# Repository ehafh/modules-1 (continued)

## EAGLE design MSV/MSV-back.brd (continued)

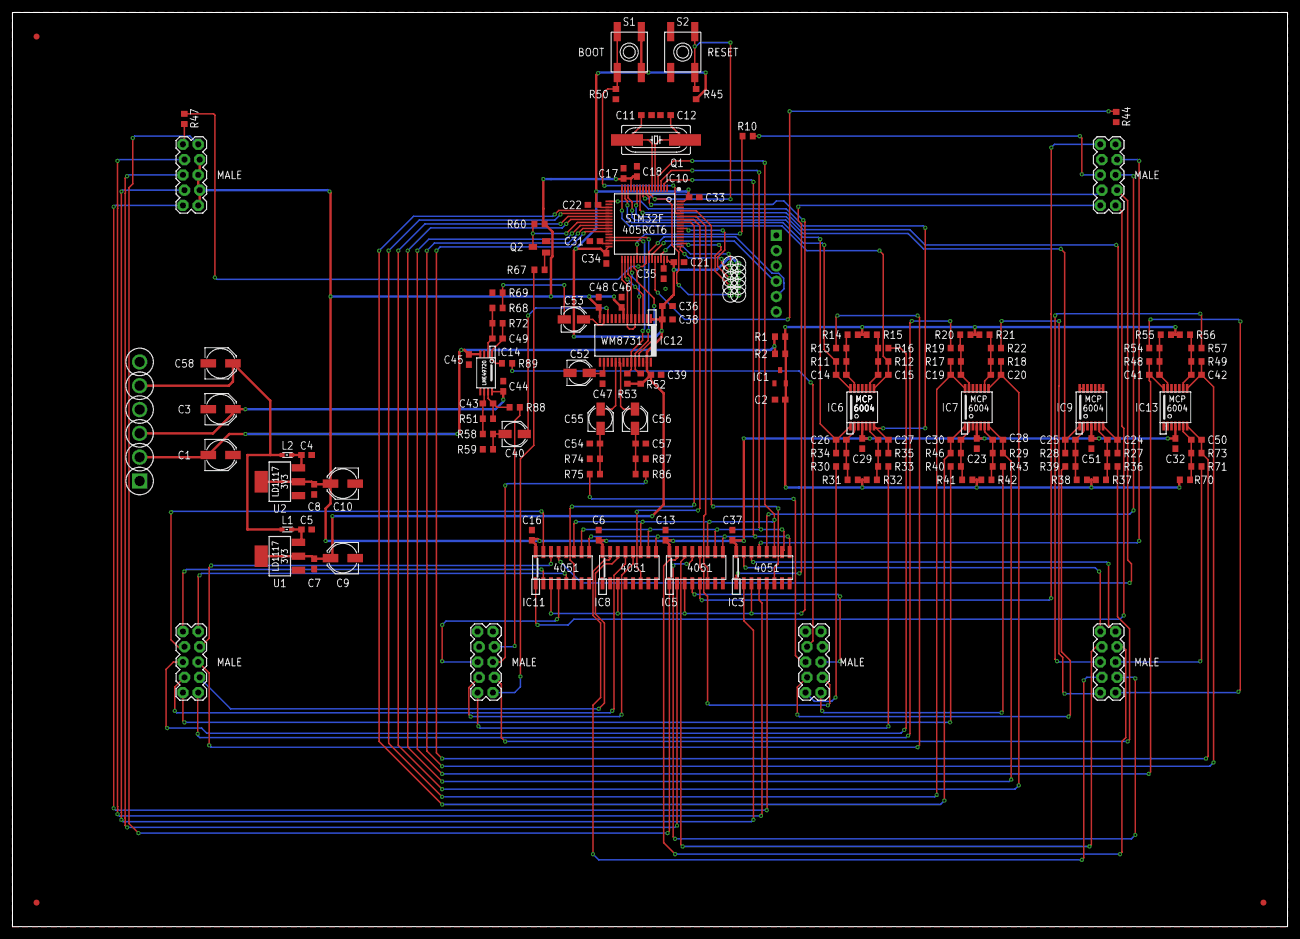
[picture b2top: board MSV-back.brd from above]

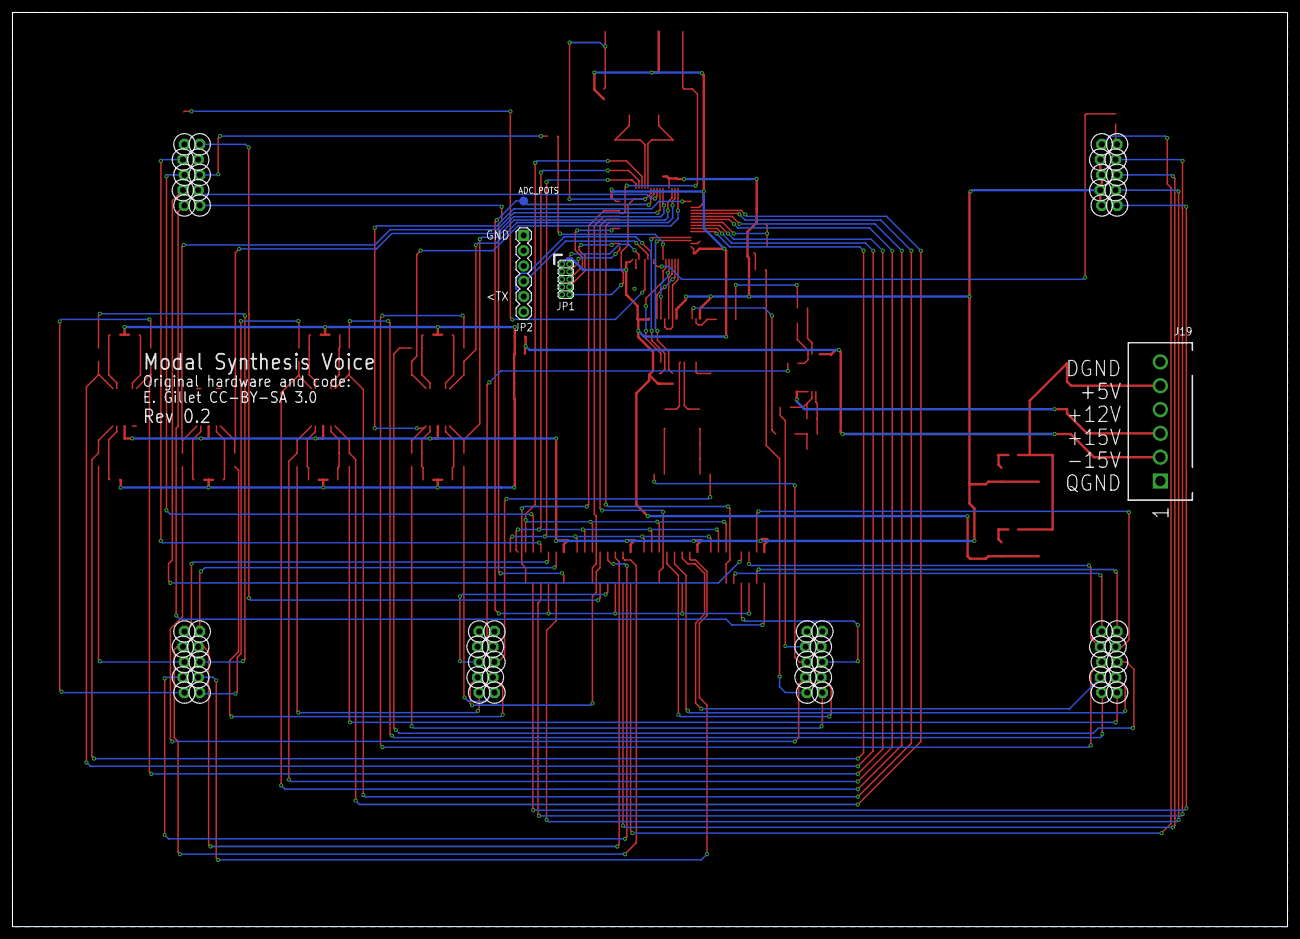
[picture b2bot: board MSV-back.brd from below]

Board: 2 copper layers, 212.0 x 152.0 mm, 153 parts (4 on the bottom side), 132 nets.

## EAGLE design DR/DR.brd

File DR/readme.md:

Overview
=======

Digital Resonator is a synthesizer module for the Buchla format, developed and manufactured by [1979](https://1979.ws/). It is based on [Rings](https://mutable-instruments.net/modules/rings/) by [Mutable Instruments](https://mutable-instruments.net/). The original source files for Rings can be found in the [Mutable Instruments](https://github.com/pichenettes/eurorack) Github repository.

Visit [1979.ws/digital-resonator](https://1979.ws/digital-resonator/) for more information.

License
=======

These schematic and PCB files are distributed under the Creative Commons [CC-BY-SA 3.0](https://creativecommons.org/licenses/by-sa/3.0/) license, the same license used by the original hardware.

CC BY-SA 3.0 does not confer the right to use intellectual property such as trademarks, brand names, and logos. 1979, Digital Resonator, Mutable Instruments, and Rings are trademarks of their respective owners and should not be used without permission.

Firmware
=======

Source code will be published soon.

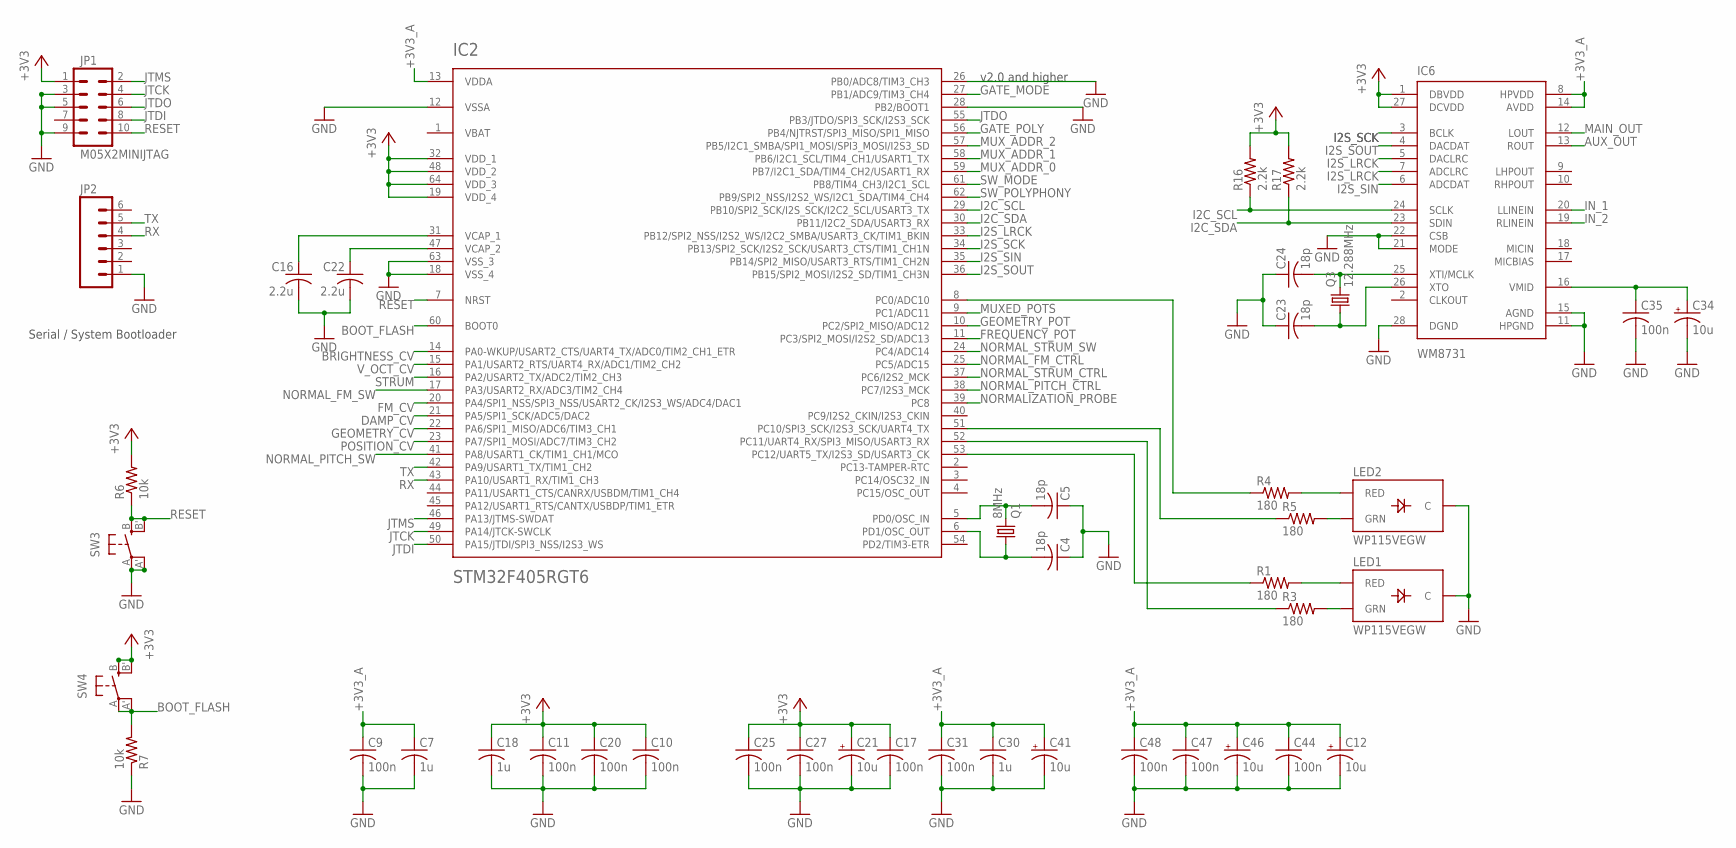
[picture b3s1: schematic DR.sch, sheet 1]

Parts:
C4, C5, C23, C24: 18p; C0603
C7, C18, C30: 1u; C0603
C9, C10, C11, C17, C20, C25, C27, C31, C35, C44, C47, C48: 100n; C0603
C12, C21, C34, C41, C46: 10u; PANASONIC_A
C16, C22: 2.2u; C0805
IC2: STM32F405RGT6; TQFP-10X10-64
IC6: WM8731; SSOP28
JP1: M05X2MINIJTAG; 2X5-1.27
JP2: M06SIP; 1X06
LED1, LED2: WP115VEGW; LED-BICOLOR-THROUGHHOLE
Q1: 8MHz; HC49UP
Q3: 12.288MHz; HC49UP
R1, R3, R4, R5: 180; R0603
R6, R7: 10k; R0603
R16, R17: 2.2k; R0603
SW3, SW4: EVQQ2; EVQ-Q2

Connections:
+3V3: C10.1, C11.1, C17.1, C18.1, C20.1, C21.+, C25.1, C27.1, IC2.19 (VDD_4), IC2.32 (VDD_1), IC2.48 (VDD_2), IC2.64 (VDD_3), IC6.1 (DBVDD), IC6.27 (DCVDD), JP1.1, R6.2, R16.2, R17.2, SW4.B (S), SW4.B' (S1); also elsewhere on the board
+3V3_A: C7.1, C9.1, C12.+, C30.1, C31.1, C41.+, C44.1, C46.+, C47.1, C48.1, IC2.13 (VDDA), IC6.8 (HPVDD), IC6.14 (AVDD); also elsewhere on the board
AUX_OUT: IC6.13 (ROUT); also elsewhere on the board
BOOT_FLASH: IC2.60 (BOOT0), R7.2, SW4.A, SW4.A' (P1)
BRIGHTNESS_CV: IC2.14 (PA0-WKUP/USART2_CTS/UART4_TX/ADC0/TIM2_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); also elsewhere on the board
DAMP_CV: IC2.21 (PA5/SPI1_SCK/ADC5/DAC2); also elsewhere on the board
FM_CV: IC2.20 (PA4/SPI1_NSS/SPI3_NSS/USART2_CK/I2S3_WS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); also elsewhere on the board
FREQUENCY_POT: IC2.11 (PC3/SPI2_MOSI/I2S2_SD/ADC13); also elsewhere on the board
GATE_MODE: IC2.27 (PB1/ADC9/TIM3_CH4); also elsewhere on the board
GATE_POLY: IC2.56 (PB4/NJTRST/SPI3_MISO/SPI1_MISO); also elsewhere on the board
GEOMETRY_CV: IC2.22 (PA6/SPI1_MISO/ADC6/TIM3_CH1); also elsewhere on the board
GEOMETRY_POT: IC2.10 (PC2/SPI2_MISO/ADC12); also elsewhere on the board
GND: C4.1, C5.1, C7.2, C9.2, C10.2, C11.2, C12.-, C16.2, C17.2, C18.2, C20.2, C21.-, C22.2, C23.1, C24.1, C25.2, C27.2, C30.2, C31.2, C34.-, C35.2, C41.-, C44.2, C46.-, C47.2, C48.2, IC2.12 (VSSA), IC2.18 (VSS_4), IC2.26 (PB0/ADC8/TIM3_CH3), IC2.28 (PB2/BOOT1), IC2.63 (VSS_3), IC6.11 (HPGND), IC6.15 (AGND), IC6.21 (MODE), IC6.22 (CSB), IC6.28 (DGND), JP1.3, JP1.5, JP1.9, JP2.1, LED1.2 (C), LED2.2 (C), R7.1, SW3.A, SW3.A' (P1); also elsewhere on the board
I2C_SCL: IC2.29 (PB10/SPI2_SCK/I2S_SCK/I2C2_SCL/USART3_TX), IC6.24 (SCLK), R16.1
I2C_SDA: IC2.30 (PB11/I2C2_SDA/USART3_RX), IC6.23 (SDIN), R17.1
I2S_LRCK: IC2.33 (PB12/SPI2_NSS/I2S2_WS/I2C2_SMBA/USART3_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), IC6.5 (DACLRC), IC6.7 (ADCLRC)
I2S_SCK: IC2.34 (PB13/SPI2_SCK/I2S2_SCK/USART3_CTS/TIM1_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), IC6.3 (BCLK)
I2S_SIN: IC2.35 (PB14/SPI2_MISO/USART3_RTS/TIM1_CH2N), IC6.6 (ADCDAT)
I2S_SOUT: IC2.36 (PB15/SPI2_MOSI/I2S2_SD/TIM1_CH3N), IC6.4 (DACDAT)
IN_1: IC6.20 (LLINEIN); also elsewhere on the board
IN_2: IC6.19 (RLINEIN); also elsewhere on the board
JTCK: IC2.49 (PA14/JTCK-SWCLK), JP1.4
JTDI: IC2.50 (PA15/JTDI/SPI3_NSS/I2S3_WS), JP1.8
JTDO: IC2.55 (PB3/JTDO/SPI3_SCK/I2S3_SCK), JP1.6
JTMS: IC2.46 (PA13/JTMS-SWDAT), JP1.2
MAIN_OUT: IC6.12 (LOUT); also elsewhere on the board
MUXED_POTS: IC2.9 (PC1/ADC11); also elsewhere on the board
MUX_ADDR_0: IC2.59 (PB7/I2C1_SDA/TIM4_CH2/USART1_RX); also elsewhere on the board
MUX_ADDR_1: IC2.58 (PB6/I2C1_SCL/TIM4_CH1/USART1_TX); also elsewhere on the board
MUX_ADDR_2: IC2.57 (PB5/I2C1_SMBA/SPI1_MOSI/SPI3_MOSI/I2S3_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); also elsewhere on the board
unnamed: C5.2, IC2.5 (PD0/OSC_IN), Q1.2
unnamed: C4.2, IC2.6 (PD1/OSC_OUT), Q1.1
unnamed: LED1.3 (RED), R1.2
unnamed: C22.1, IC2.47 (VCAP_2)
unnamed: C34.+, C35.1, IC6.16 (VMID)
unnamed: C16.1, IC2.31 (VCAP_1)
unnamed: LED1.1 (GRN), R3.2
unnamed: LED2.3 (RED), R4.2
unnamed: LED2.1 (GRN), R5.2
unnamed: IC2.52 (PC11/UART4_RX/SPI3_MISO/USART3_RX), R3.1
unnamed: IC2.8 (PC0/ADC10), R4.1
unnamed: C24.2, IC6.25 (XTI/MCLK), Q3.2
unnamed: C23.2, IC6.26 (XTO), Q3.1
unnamed: IC2.53 (PC12/UART5_TX/I2S3_SD/USART3_CK), R1.1
unnamed: IC2.51 (PC10/SPI3_SCK/I2S3_SCK/UART4_TX), R5.1
NORMALIZATION_PROBE: IC2.39 (PC8); also elsewhere on the board
NORMAL_FM_CTRL: IC2.25 (PC5/ADC15); also elsewhere on the board
NORMAL_FM_SW: IC2.17 (PA3/USART2_RX/ADC3/TIM2_CH4); also elsewhere on the board
NORMAL_PITCH_CTRL: IC2.38 (PC7/I2S3_MCK); also elsewhere on the board
NORMAL_PITCH_SW: IC2.41 (PA8/USART1_CK/TIM1_CH1/MCO); also elsewhere on the board
NORMAL_STRUM_CTRL: IC2.37 (PC6/I2S2_MCK); also elsewhere on the board
NORMAL_STRUM_SW: IC2.24 (PC4/ADC14); also elsewhere on the board
POSITION_CV: IC2.23 (PA7/SPI1_MOSI/ADC7/TIM3_CH2); also elsewhere on the board
RESET: IC2.7 (NRST), JP1.10, R6.1, SW3.B (S), SW3.B' (S1)
RX: IC2.43 (PA10/USART1_RX/TIM1_CH3), JP2.4
STRUM: IC2.16 (PA2/USART2_TX/ADC2/TIM2_CH3); also elsewhere on the board
SW_MODE: IC2.61 (PB8/TIM4_CH3/I2C1_SCL); also elsewhere on the board
SW_POLYPHONY: IC2.62 (PB9/SPI2_NSS/I2S2_WS/I2C1_SDA/TIM4_CH4); also elsewhere on the board
TX: IC2.42 (PA9/USART1_TX/TIM1_CH2), JP2.5
VBAT: IC2.1 (VBAT)
V_OCT_CV: IC2.15 (PA1/USART2_RTS/UART4_RX/ADC1/TIM2_CH2); also elsewhere on the board

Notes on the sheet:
Serial / System Bootloader
v2.0 and higher

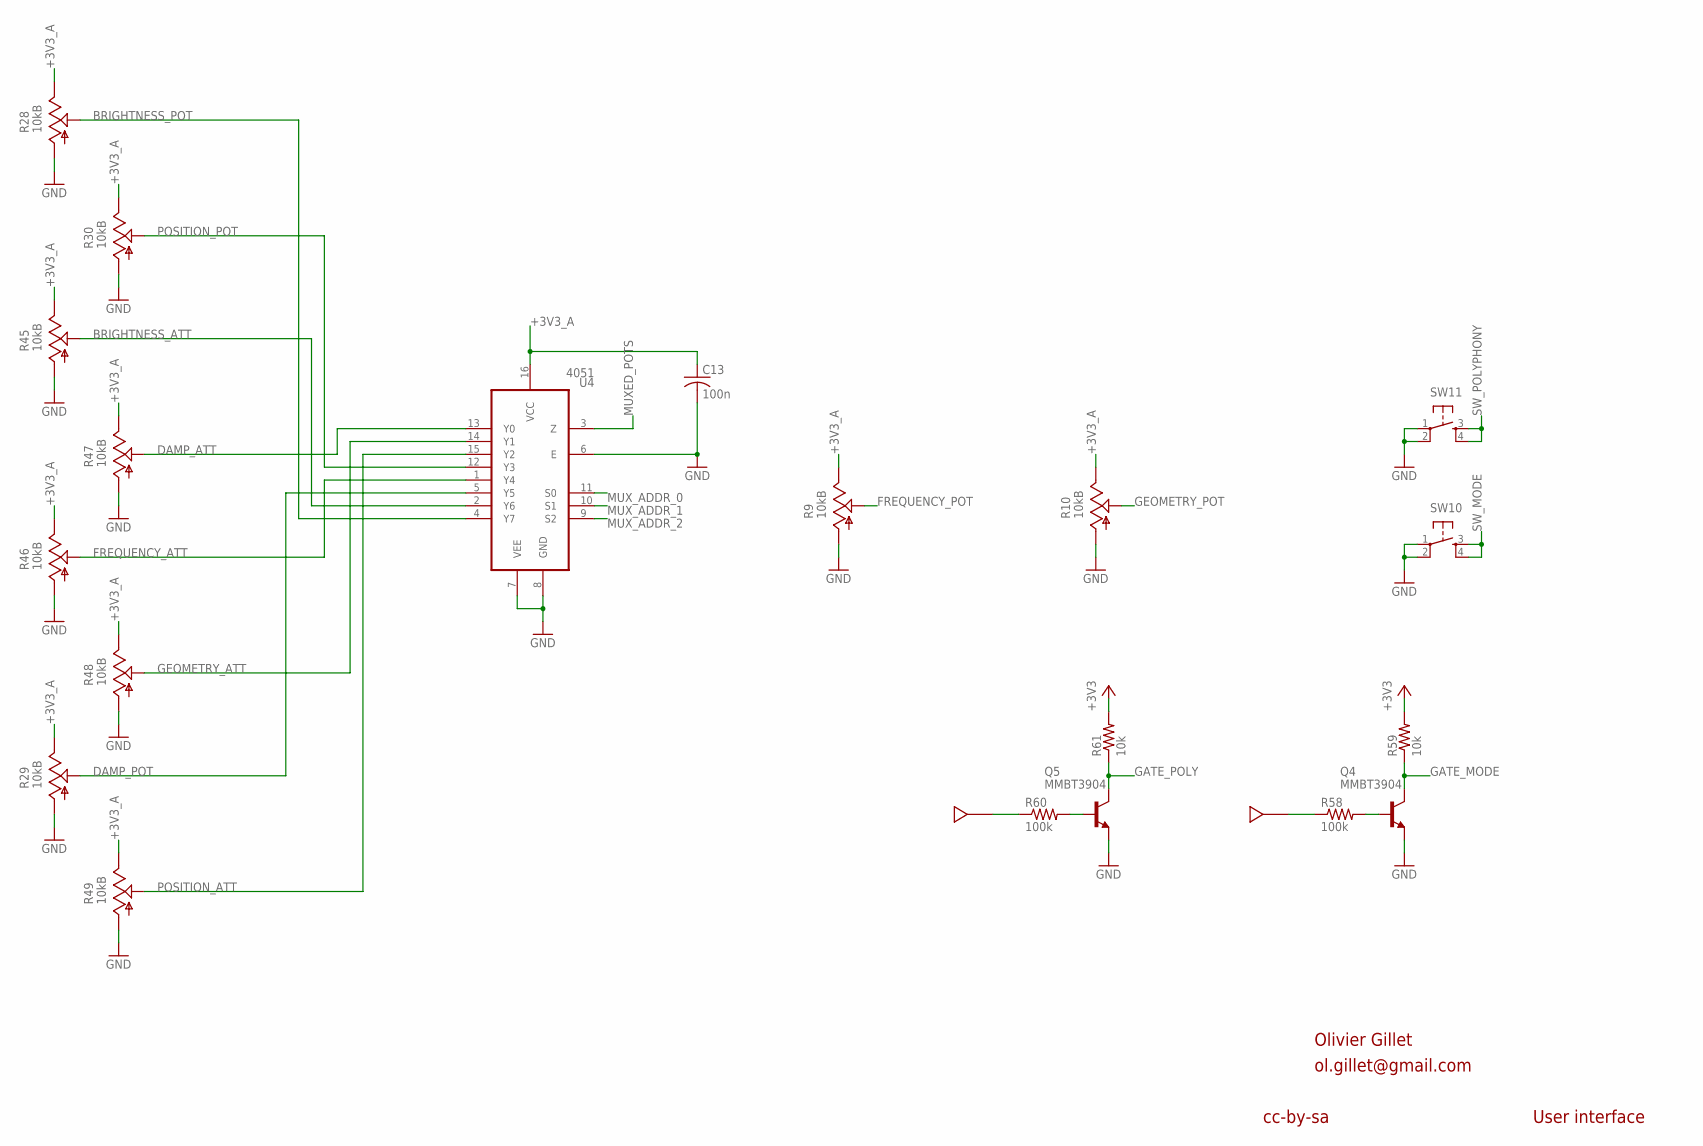
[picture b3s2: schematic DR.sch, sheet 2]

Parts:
C13: 100n; C0603
J7, J13: JOHNSON_BANANASTD; JOHNSON
Q4, Q5: MMBT3904; SOT23-BEC
R9, R10, R28, R29, R30: 10kB; ALPS_POT_VERTICAL_PS
R45, R46, R47, R48, R49: 10kB; ALPS_POT_VERTICAL
R58, R60: 100k; R0603
R59, R61: 10k; R0603
SW10, SW11: TAC_SWITCH; C&K_D6R
U4: 4051; SO16

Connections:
+3V3: R59.2, R61.2; also elsewhere on the board
+3V3_A: C13.1, R9.P$1 (E), R10.P$1 (E), R28.P$1 (E), R29.P$1 (E), R30.P$1 (E), R45.P$1 (E), R46.P$1 (E), R47.P$1 (E), R48.P$1 (E), R49.P$1 (E), U4.16 (VCC); also elsewhere on the board
BRIGHTNESS_ATT: R45.P$2 (S), U4.2 (Y6)
BRIGHTNESS_POT: R28.P$2 (S), U4.4 (Y7)
DAMP_ATT: R47.P$2 (S), U4.13 (Y0)
DAMP_POT: R29.P$2 (S), U4.5 (Y5)
FREQUENCY_ATT: R46.P$2 (S), U4.1 (Y4)
FREQUENCY_POT: R9.P$2 (S); also elsewhere on the board
GATE_MODE: Q4.C, R59.1; also elsewhere on the board
GATE_POLY: Q5.C, R61.1; also elsewhere on the board
GEOMETRY_ATT: R48.P$2 (S), U4.14 (Y1)
GEOMETRY_POT: R10.P$2 (S); also elsewhere on the board
GND: C13.2, Q4.E, Q5.E, R9.P$3 (A), R10.P$3 (A), R28.P$3 (A), R29.P$3 (A), R30.P$3 (A), R45.P$3 (A), R46.P$3 (A), R47.P$3 (A), R48.P$3 (A), R49.P$3 (A), SW10.1, SW10.2, SW11.1, SW11.2, U4.6 (E), U4.7 (VEE), U4.8 (GND); also elsewhere on the board
MUXED_POTS: U4.3 (Z); also elsewhere on the board
MUX_ADDR_0: U4.11 (S0); also elsewhere on the board
MUX_ADDR_1: U4.10 (S1); also elsewhere on the board
MUX_ADDR_2: U4.9 (S2); also elsewhere on the board
unnamed: Q4.B, R58.2
unnamed: Q5.B, R60.2
unnamed: J7.1, R58.1
unnamed: J13.1, R60.1
POSITION_ATT: R49.P$2 (S), U4.15 (Y2)
POSITION_POT: R30.P$2 (S), U4.12 (Y3)
SW_MODE: SW10.3, SW10.4; also elsewhere on the board
SW_POLYPHONY: SW11.3, SW11.4; also elsewhere on the board

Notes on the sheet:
cc-by-sa
Olivier Gillet
ol.gillet@gmail.com
User interface

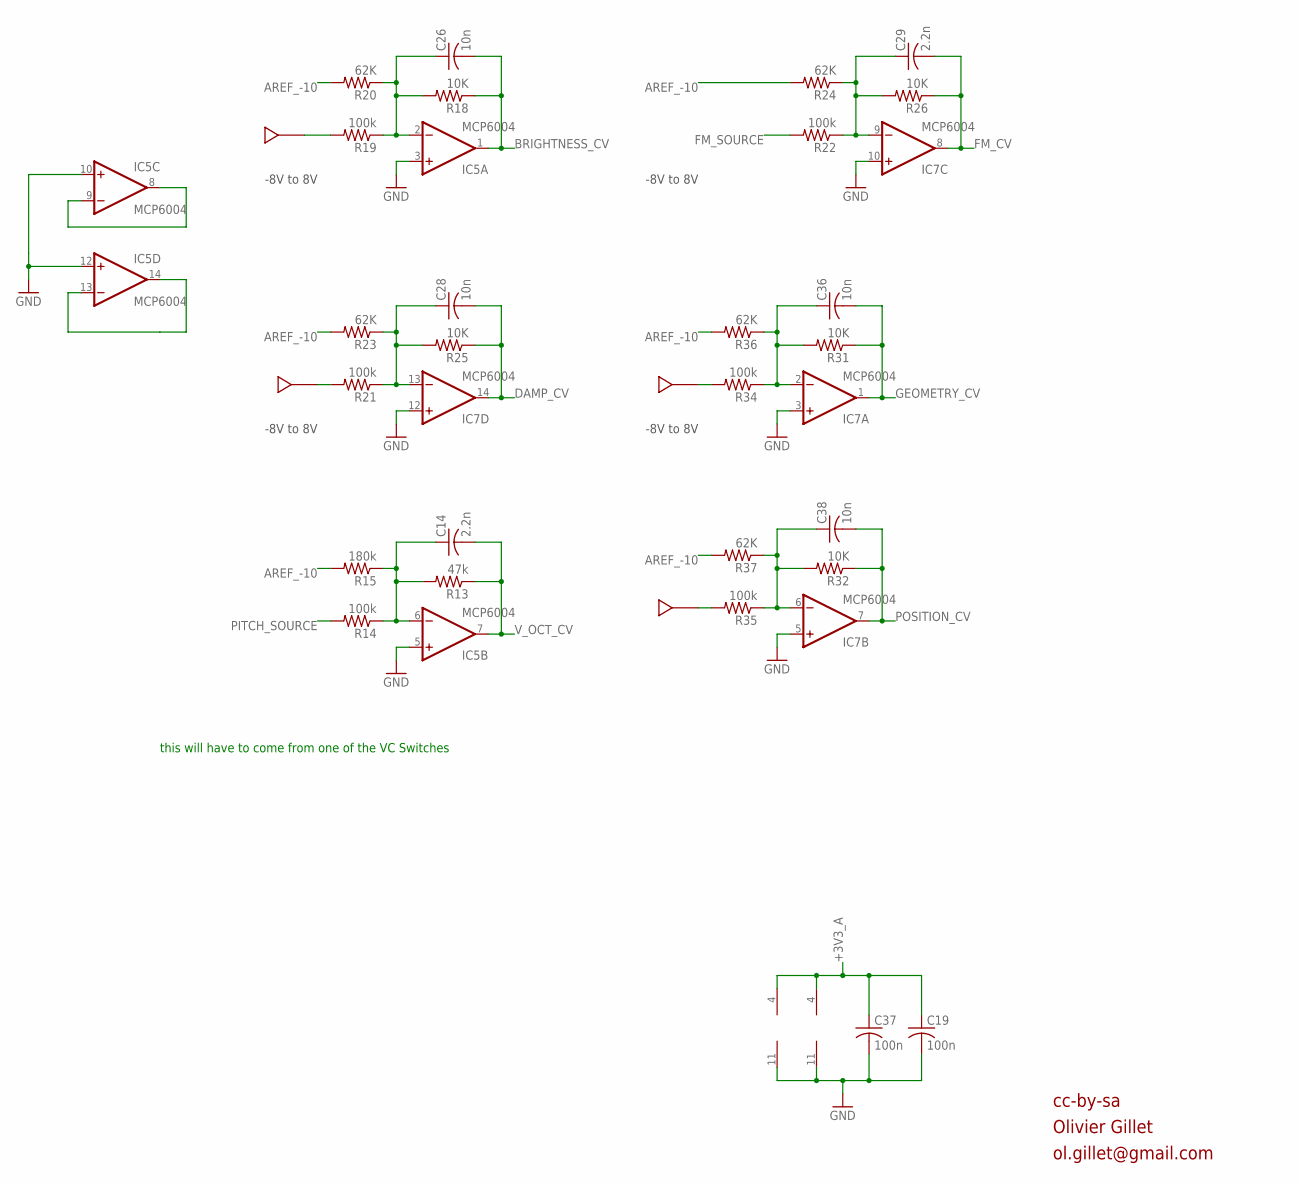
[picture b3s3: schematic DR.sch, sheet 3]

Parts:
C14, C29: 2.2n; C0603
C19, C37: 100n; C0603
C26, C28, C36, C38: 10n; C0603
IC5, IC7: MCP6004; SO14
J1, J3, J4, J14: JOHNSON_BANANASTD; JOHNSON
R13: 47k; R0603
R14, R19, R21, R22, R34, R35: 100k; R0603
R15: 180k; R0603
R18, R25, R26, R31, R32: 10K; R0603
R20, R23, R24, R36, R37: 62K; R0603

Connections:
+3V3_A: C19.1, C37.1, IC5.4 (V+), IC7.4 (V+); also elsewhere on the board
AREF_-10: R15.2, R20.2, R23.2, R24.2, R36.2, R37.2; also elsewhere on the board
BRIGHTNESS_CV: C26.2, IC5.1 (OUT), R18.1; also elsewhere on the board
DAMP_CV: C28.2, IC7.14 (OUT), R25.1; also elsewhere on the board
FM_CV: C29.2, IC7.8 (OUT), R26.1; also elsewhere on the board
FM_SOURCE: R22.2; also elsewhere on the board
GEOMETRY_CV: C36.2, IC7.1 (OUT), R31.1; also elsewhere on the board
GND: C19.2, C37.2, IC5.3 (+IN), IC5.5 (+IN), IC5.10 (+IN), IC5.11 (V-), IC5.12 (+IN), IC7.3 (+IN), IC7.5 (+IN), IC7.10 (+IN), IC7.11 (V-), IC7.12 (+IN); also elsewhere on the board
unnamed: J14.1, R19.2
unnamed: C26.1, IC5.2 (-IN), R18.2, R19.1, R20.1
unnamed: C29.1, IC7.9 (-IN), R22.1, R24.1, R26.2
unnamed: J4.1, R34.2
unnamed: J1.1, R21.2
unnamed: C28.1, IC7.13 (-IN), R21.1, R23.1, R25.2
unnamed: C14.1, IC5.6 (-IN), R13.2, R14.1, R15.1
unnamed: C36.1, IC7.2 (-IN), R31.2, R34.1, R36.1
unnamed: J3.1, R35.2
unnamed: C38.1, IC7.6 (-IN), R32.2, R35.1, R37.1
unnamed: IC5.13 (-IN), IC5.14 (OUT)
unnamed: IC5.8 (OUT), IC5.9 (-IN)
PITCH_SOURCE: R14.2; also elsewhere on the board
POSITION_CV: C38.2, IC7.7 (OUT), R32.1; also elsewhere on the board
V_OCT_CV: C14.2, IC5.7 (OUT), R13.1; also elsewhere on the board

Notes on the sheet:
cc-by-sa
Olivier Gillet
ol.gillet@gmail.com
-8V to 8V
this will have to come from one of the VC Switches

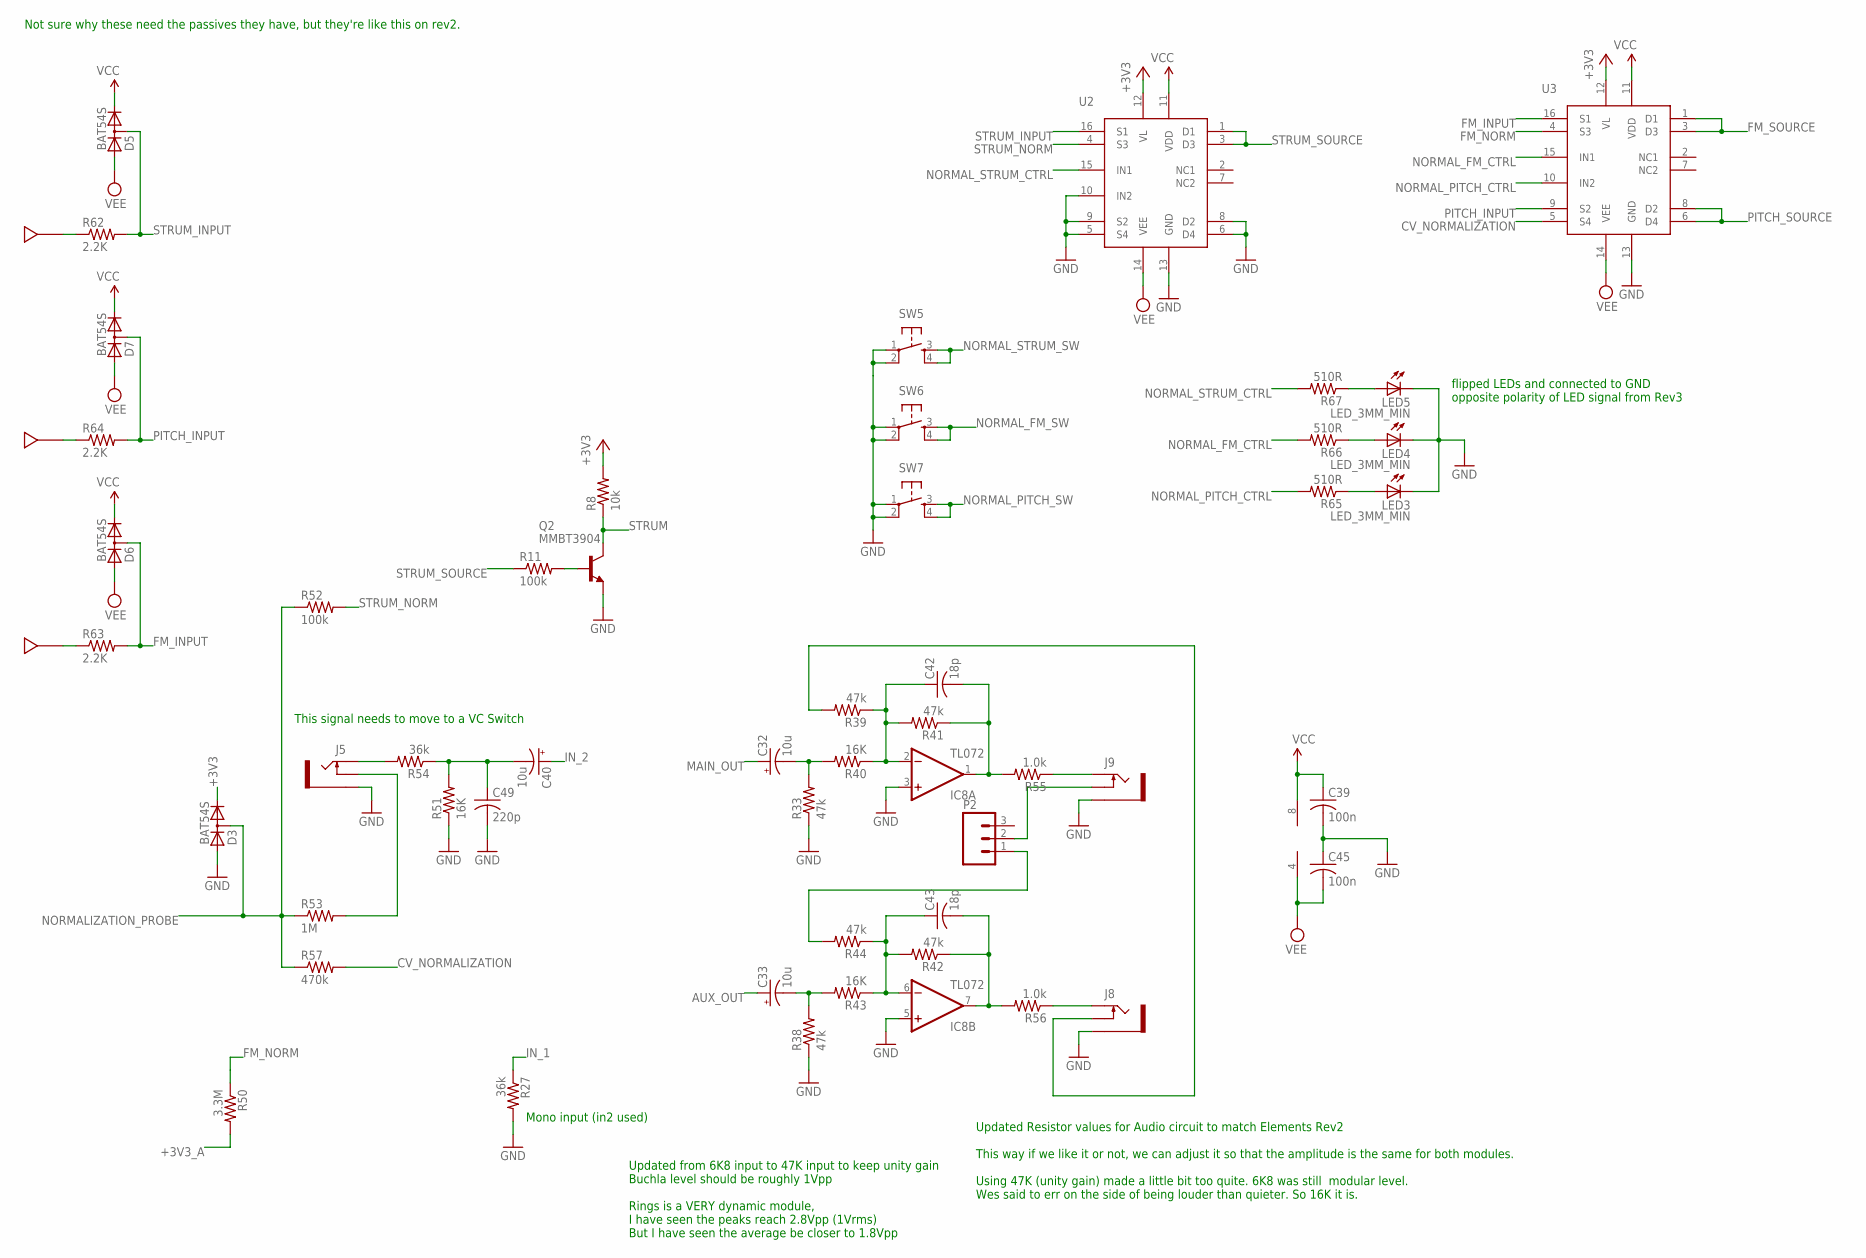
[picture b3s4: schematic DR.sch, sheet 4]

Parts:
C32, C33, C40: 10u; PANASONIC_A
C39, C45: 100n; C0603
C42, C43: 18p; C0603
C49: 220p; C0603
D3, D5, D6, D7: BAT54S; SOT23
IC8: TL072; SO08
J2, J6, J12: JOHNSON_BANANASTD; JOHNSON
J5, J8, J9: SWITCHCRAFT_42A; SWITCH_JOHNSON
LED3, LED4, LED5: LED_3MM_MIN
P2: M03LOCK; 1X03_LOCK
Q2: MMBT3904; SOT23-BEC
R8: 10k; R0603
R11, R52: 100k; R0603
R27, R54: 36k; R0603
R33, R38, R39, R41, R42, R44: 47k; R0603
R40, R43, R51: 16K; R0603
R50: 3.3M; R0603
R53: 1M; R0603
R55, R56: 1.0k; R0603
R57: 470k; R0603
R62, R63, R64: 2.2K; R0603
R65, R66, R67: 510R; R0603
SW5, SW6, SW7: TAC_SWITCHPTH; TACTILE-PTH
U2, U3: DG403_ANALOG_SWITCH; SO16

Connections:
+3V3: D3.2 (C), R8.2, U2.12 (VL), U3.12 (VL); also elsewhere on the board
+3V3_A: R50.2; also elsewhere on the board
AUX_OUT: C33.+; also elsewhere on the board
CV_NORMALIZATION: R57.2, U3.5 (S4)
FM_INPUT: D6.3 (AC), R63.2, U3.16 (S1)
FM_NORM: R50.1, U3.4 (S3)
FM_SOURCE: U3.1 (D1), U3.3 (D3); also elsewhere on the board
GND: C39.2, C45.1, C49.2, D3.1 (A), IC8.3 (+IN), IC8.5 (+IN), J5.G (1), J8.G (1), J9.G (1), LED3.K (C), LED4.K (C), LED5.K (C), Q2.E, R27.2, R33.1, R38.1, R51.1, SW5.1, SW5.2, SW6.1, SW6.2, SW7.1, SW7.2, U2.5 (S4), U2.6 (D4), U2.8 (D2), U2.9 (S2), U2.10 (IN2), U2.13 (GND), U3.13 (GND); also elsewhere on the board
IN_1: R27.1; also elsewhere on the board
IN_2: C40.+; also elsewhere on the board
MAIN_OUT: C32.+; also elsewhere on the board
unnamed: C40.-, C49.1, R51.2, R54.1
unnamed: J5.S (3), R54.2
unnamed: C33.-, R38.2, R43.2
unnamed: LED5.A, R67.1
unnamed: C43.1, IC8.6 (-IN), R42.2, R43.1, R44.1
unnamed: C43.2, IC8.7 (OUT), R42.1, R56.2
unnamed: J8.S (3), R56.1
unnamed: C32.-, R33.2, R40.2
unnamed: C42.1, IC8.2 (-IN), R39.1, R40.1, R41.2
unnamed: C42.2, IC8.1 (OUT), R41.1, R55.2
unnamed: J9.S (3), R55.1
unnamed: LED4.A, R66.1
unnamed: J12.1, R62.1
unnamed: J5.C (2), R53.2
unnamed: J8.C (2), R39.2
unnamed: P2.1, R44.2
unnamed: J9.C (2), P2.2
unnamed: LED3.A, R65.1
unnamed: J2.1, R63.1
unnamed: J6.1, R64.1
unnamed: Q2.B, R11.2
NORMALIZATION_PROBE: D3.3 (AC), R52.1, R53.1, R57.1; also elsewhere on the board
NORMAL_FM_CTRL: R66.2, U3.15 (IN1); also elsewhere on the board
NORMAL_FM_SW: SW6.3, SW6.4; also elsewhere on the board
NORMAL_PITCH_CTRL: R65.2, U3.10 (IN2); also elsewhere on the board
NORMAL_PITCH_SW: SW7.3, SW7.4; also elsewhere on the board
NORMAL_STRUM_CTRL: R67.2, U2.15 (IN1); also elsewhere on the board
NORMAL_STRUM_SW: SW5.3, SW5.4; also elsewhere on the board
PITCH_INPUT: D7.3 (AC), R64.2, U3.9 (S2)
PITCH_SOURCE: U3.6 (D4), U3.8 (D2); also elsewhere on the board
STRUM: Q2.C, R8.1; also elsewhere on the board
STRUM_INPUT: D5.3 (AC), R62.2, U2.16 (S1)
STRUM_NORM: R52.2, U2.4 (S3)
STRUM_SOURCE: R11.1, U2.1 (D1), U2.3 (D3)
VCC: C39.1, D5.2 (C), D6.2 (C), D7.2 (C), IC8.8 (V+), U2.11 (VDD), U3.11 (VDD); also elsewhere on the board
VEE: C45.2, D5.1 (A), D6.1 (A), D7.1 (A), IC8.4 (V-), U2.14 (VEE), U3.14 (VEE); also elsewhere on the board

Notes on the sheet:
This signal needs to move to a VC Switch
Not sure why these need the passives they have, but they're like this on rev2.
Mono input (in2 used)
flipped LEDs and connected to GND opposite polarity of LED signal from Rev3
Updated from 6K8 input to 47K input to keep unity gain Buchla level should be roughly 1Vpp Rings is a VERY dynamic module, I have seen the peaks reach 2.8Vpp (1Vrms) But I have seen the average be closer to 1.8Vpp
Updated Resistor values for Audio circuit to match Elements Rev2 This way if we like it or not, we can adjust it so that the amplitude is the same for both modules. Using 47K (unity gain) made a little bit too quite. 6K8 was still modular level. Wes said to err on the side of being louder than quie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

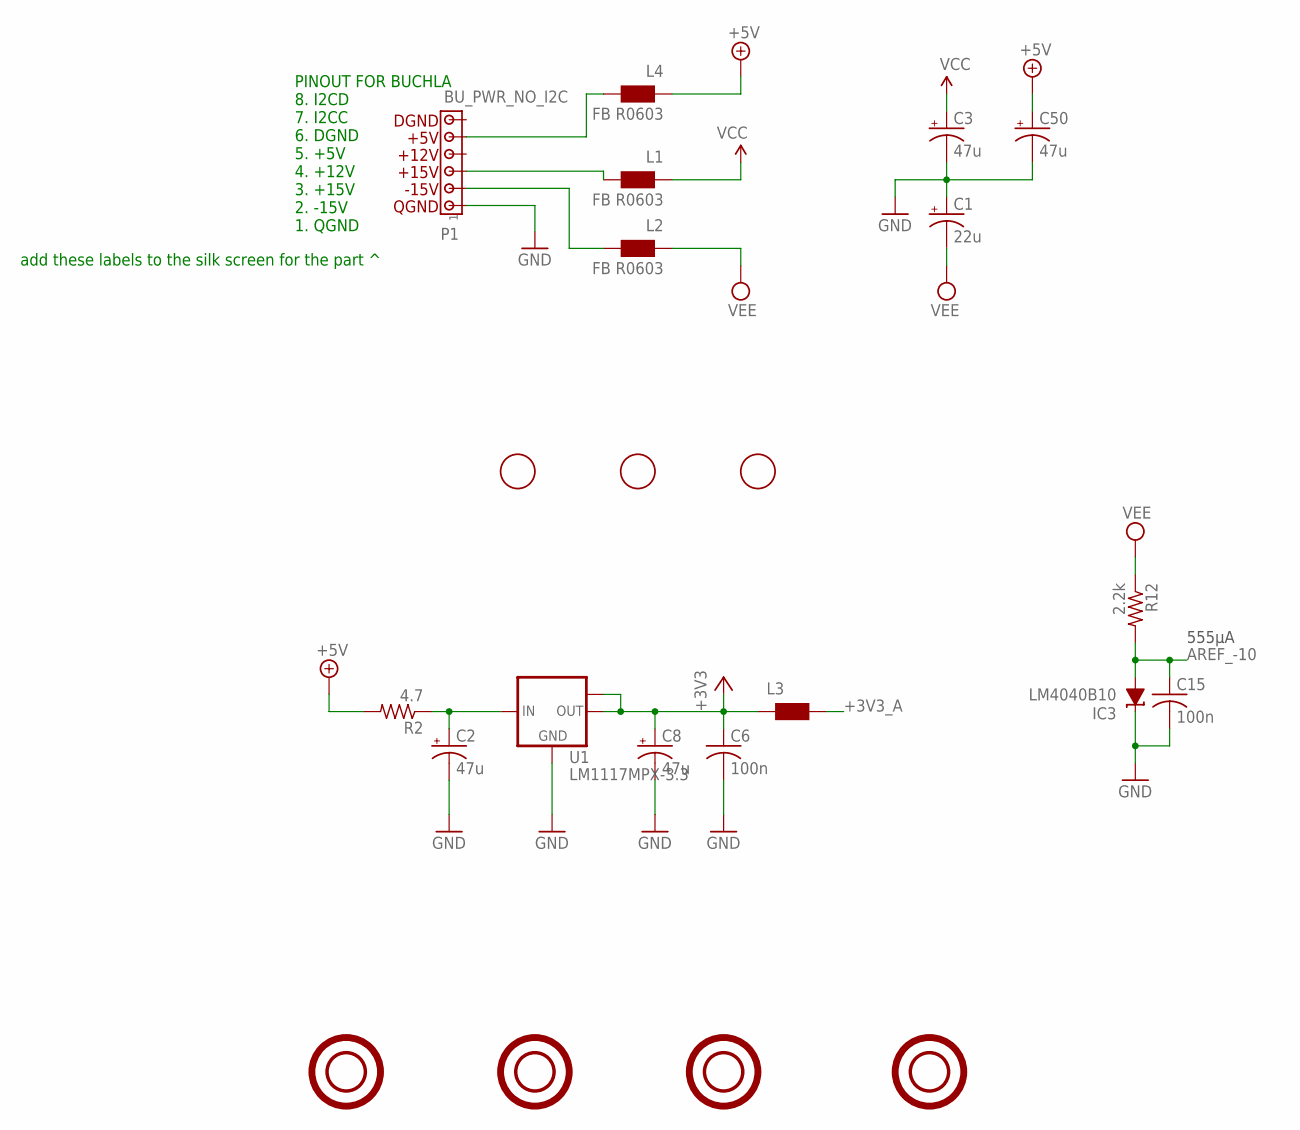
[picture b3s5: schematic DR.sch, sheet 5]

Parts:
C1: 22u; PANASONIC_C
C2, C3, C8, C50: 47u; PANASONIC_D
C6, C15: 100n; C0603
FD1, FD2, FD3: FIDUCIAL; FIDUCIAL_1MM
H1, H2, H3, H4: 3MM_MOUNT_HOLE; 3,0-PAD
IC3: LM4040B10; DBZ_R-PDSO-G3
L1, L2, L4: FB R0603; 0603
L3: WE-CBF_0603; 0603
P1: BU_PWR_NO_I2C; MTA_156
R2: 4.7; R1206
R12: 2.2k; R0603
U1: LM1117MPX-3.3; SOT223

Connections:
+3V3: C6.1, C8.+, L3.1, U1.2 (OUT), U1.TAB (OUT1); also elsewhere on the board
+3V3_A: L3.2; also elsewhere on the board
+5V: C50.+, L4.1, R2.2
AREF_-10: C15.1, IC3.2 (A), R12.2; also elsewhere on the board
GND: C1.+, C2.-, C3.-, C6.2, C8.-, C15.2, C50.-, IC3.1 (C), P1.1, U1.1 (GND); also elsewhere on the board
unnamed: C2.+, R2.1, U1.3 (IN)
unnamed: L2.2, P1.2
unnamed: L4.2, P1.5
unnamed: L1.2, P1.3
VCC: C3.+, L1.1; also elsewhere on the board
VEE: C1.-, L2.1, R12.1; also elsewhere on the board

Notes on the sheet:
555µA
PINOUT FOR BUCHLA 8. I2CD 7. I2CC 6. DGND 5. +5V 4. +12V 3. +15V 2. -15V 1. QGND
add these labels to the silk screen for the part ^

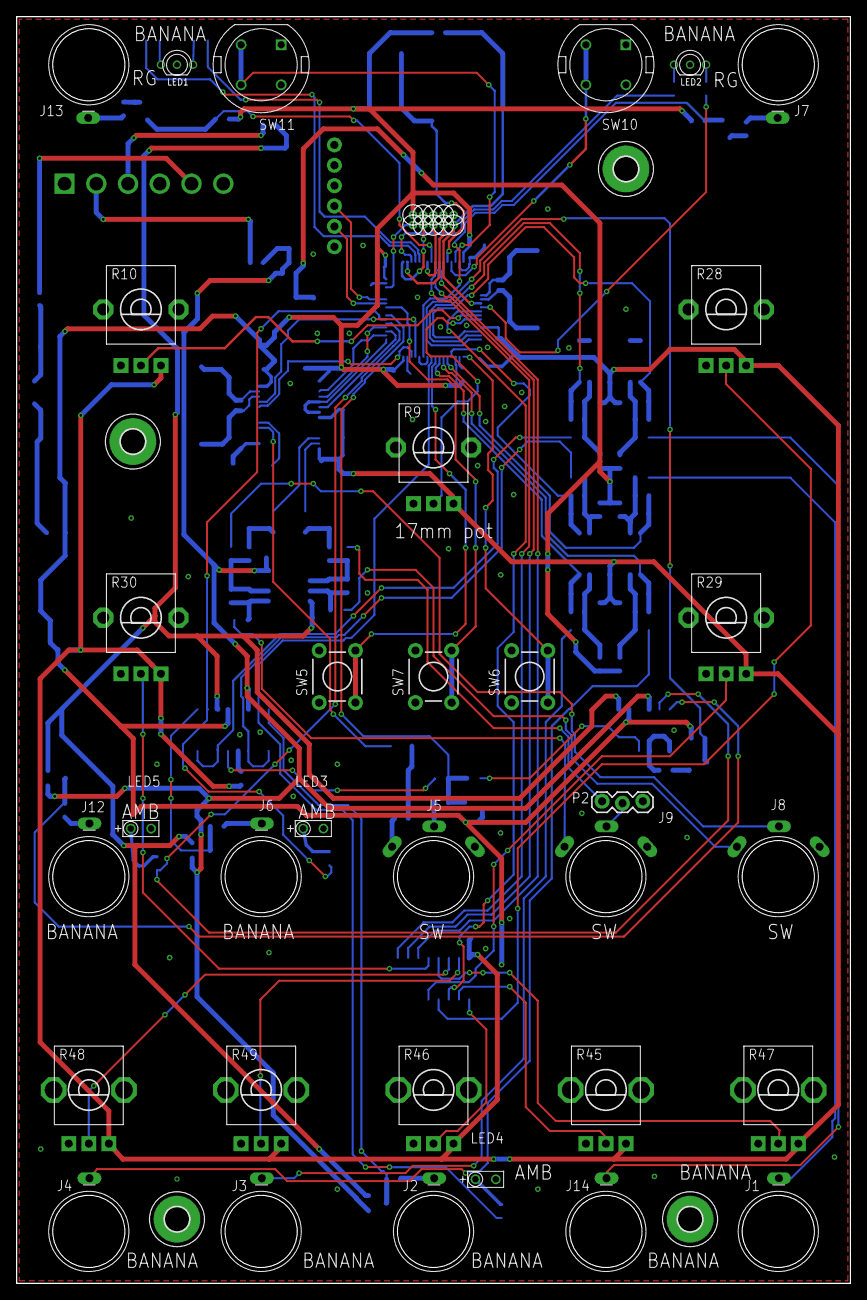
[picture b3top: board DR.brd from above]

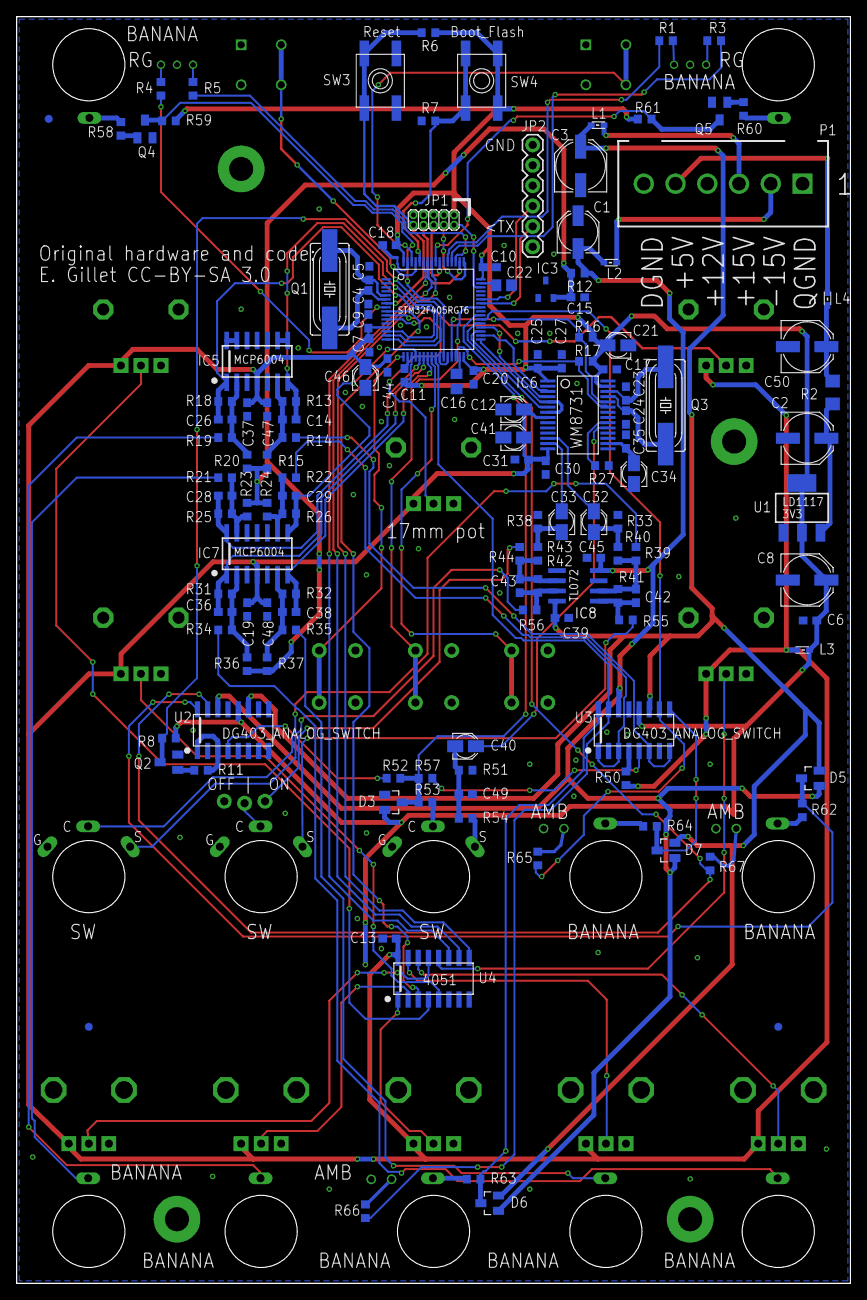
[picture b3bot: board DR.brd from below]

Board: 2 copper layers, 104.0 x 158.0 mm, 175 parts (138 on the bottom side), 122 nets.
